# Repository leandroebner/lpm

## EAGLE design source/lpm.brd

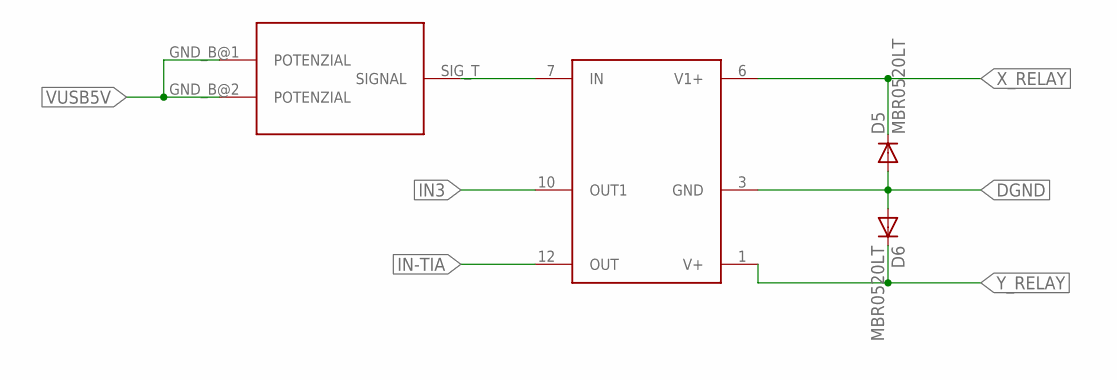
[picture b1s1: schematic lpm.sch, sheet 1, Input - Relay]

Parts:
D5, D6: MBR0520LT; SOD123
RELAY: DS1E; DIP12_8MM_X_13MM_DS1E
U$8: SMA_RAND; SMA-RAND-PRINT

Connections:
DGND: D5.A, D6.A, RELAY.3 (GND); also elsewhere on the board
IN3: RELAY.10 (OUT1); also elsewhere on the board
IN-TIA: RELAY.12 (OUT); also elsewhere on the board
IPD: RELAY.7 (IN), U$8.SIG_T (SIGNAL)
VUSB5V: U$8.GND_B@1 (POTENZIAL), U$8.GND_B@2 (POTENZIAL); also elsewhere on the board
X_RELAY: D5.C, RELAY.6 (V1+); also elsewhere on the board
Y_RELAY: D6.C, RELAY.1 (V+); also elsewhere on the board

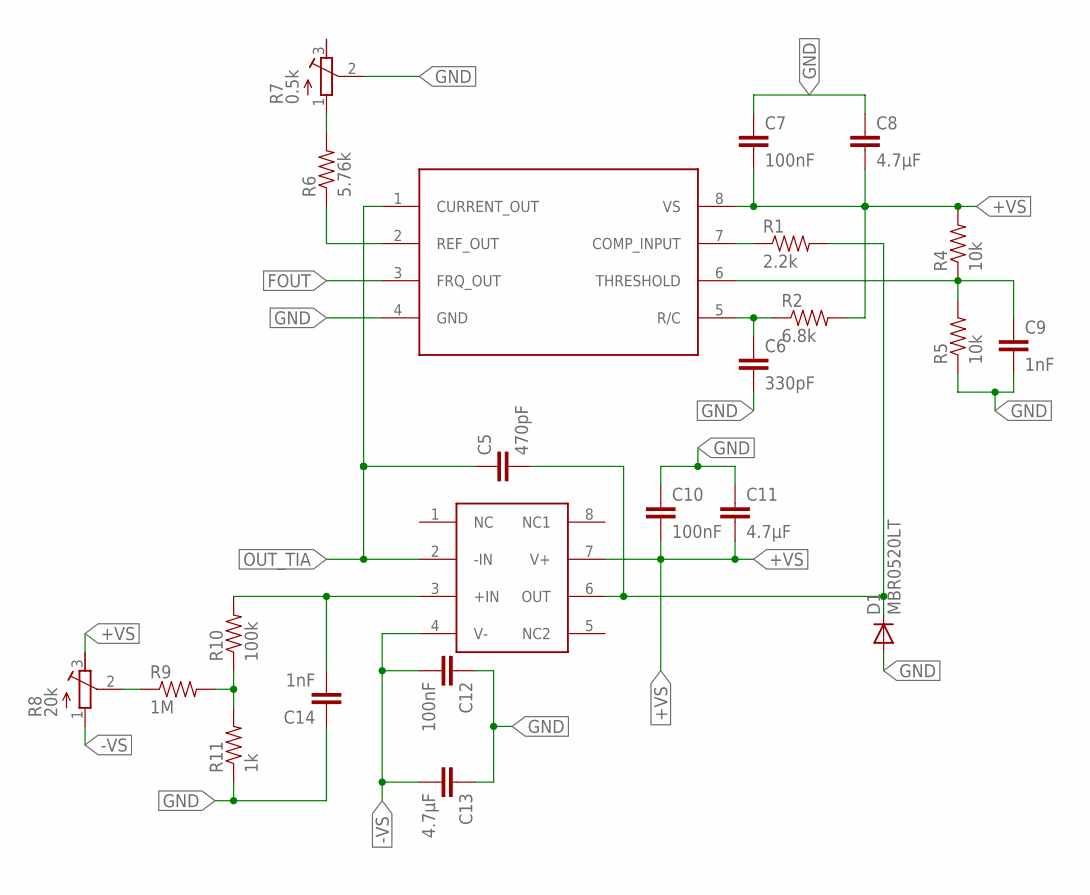
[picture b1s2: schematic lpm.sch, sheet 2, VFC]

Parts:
C5: 470pF; 0603-CAP
C6: 330pF; C0603K
C7, C10, C12: 100nF; C0603K
C8, C11, C13: 4.7µF; C0603K
C9, C14: 1nF; C0603K
D1: MBR0520LT; SOD123
R1: 2.2k; 0603-RES
R2: 6.8k; 0805
R4, R5: 10k; 0603-RES
R6: 5.76k; 0603-RES
R7: 0.5k; RTRIMTSM53YL
R8: 20k; RTRIMTS63Y
R9: 1M; 0603-RES
R10: 100k; 0603-RES
R11: 1k; 0603-RES
U$10: OPA191; SOIC8_4.90MMX3.91MM
VFC: LM331; DIP-08

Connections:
+VS: C7.2, C8.2, C10.2, C11.2, R2.2, R4.2, R8.3 (E), U$10.7 (V+), VFC.8 (VS); also elsewhere on the board
-VS: C12.2, C13.2, R8.1 (A), U$10.4 (V-); also elsewhere on the board
COMP_IN: R1.1, VFC.7 (COMP_INPUT)
FOUT: VFC.3 (FRQ_OUT); also elsewhere on the board
GND: C6.2, C7.1, C8.1, C9.2, C10.1, C11.1, C12.1, C13.1, C14.1, D1.A, R5.1, R7.2 (S), R11.1, VFC.4 (GND); also elsewhere on the board
IN+INTE: C14.2, R10.2, U$10.3 (+IN)
unnamed: C5.2, D1.C, R1.2, U$10.6 (OUT)
unnamed: C6.1, R2.1, VFC.5 (R/C)
unnamed: R6.1, VFC.2 (REF_OUT)
unnamed: C9.1, R4.1, R5.2, VFC.6 (THRESHOLD)
unnamed: R6.2, R7.1 (A)
unnamed: R9.2, R10.1, R11.2
unnamed: R8.2 (S), R9.1
OUT_TIA: C5.1, U$10.2 (-IN), VFC.1 (CURRENT_OUT); also elsewhere on the board

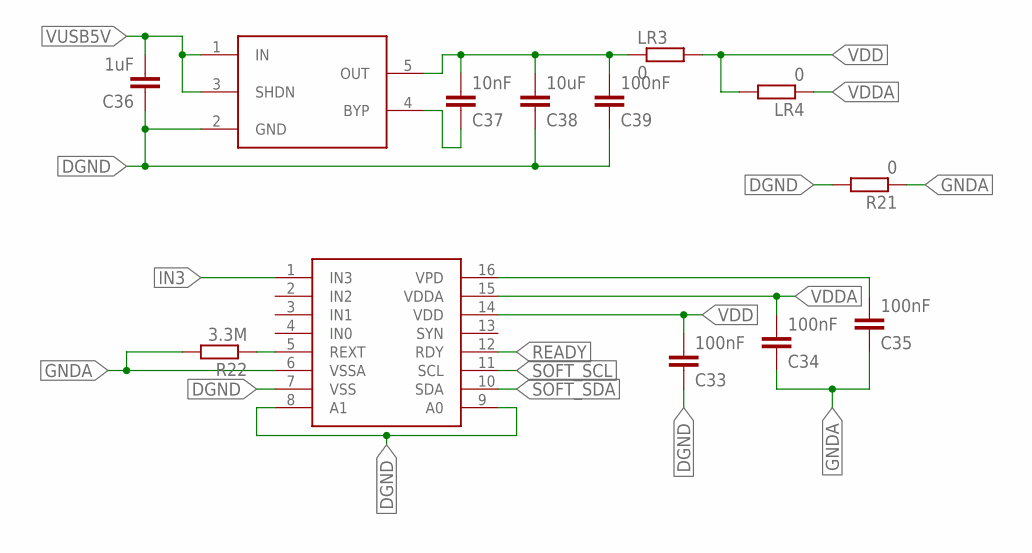
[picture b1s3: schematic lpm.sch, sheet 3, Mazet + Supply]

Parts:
C33, C34, C35, C39: 100nF; C0603
C36: 1uF; C0603
C37: 10nF; C0603
C38: 10uF; C0603
LDO1: LT1761; TSOT23-5
LR3, LR4: 0; R0603
MCDC01: MCDC04; SSOP16
R21: 0; R0603
R22: 3.3M; R0603

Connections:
DGND: C33.1, C36.1, C38.1, C39.1, LDO1.2 (GND), MCDC01.7 (VSS), MCDC01.8 (A1), MCDC01.9 (A0), R21.2; also elsewhere on the board
GNDA: C34.1, C35.1, MCDC01.6 (VSSA), R21.1, R22.2
IN3: MCDC01.1 (IN3); also elsewhere on the board
LDO_OUT3V1: C37.2, C38.2, C39.2, LDO1.5 (OUT), LR3.1
unnamed: C37.1, LDO1.4 (BYP)
READY: MCDC01.12 (RDY); also elsewhere on the board
REXT: MCDC01.5 (REXT), R22.1
SOFT_SCL: MCDC01.11 (SCL); also elsewhere on the board
SOFT_SDA: MCDC01.10 (SDA); also elsewhere on the board
VDD: C33.2, LR3.2, LR4.2, MCDC01.14 (VDD)
VDDA: C34.2, LR4.1, MCDC01.15 (VDDA)
VPD: C35.2, MCDC01.16 (VPD)
VUSB5V: C36.2, LDO1.1 (IN), LDO1.3 (SHDN); also elsewhere on the board

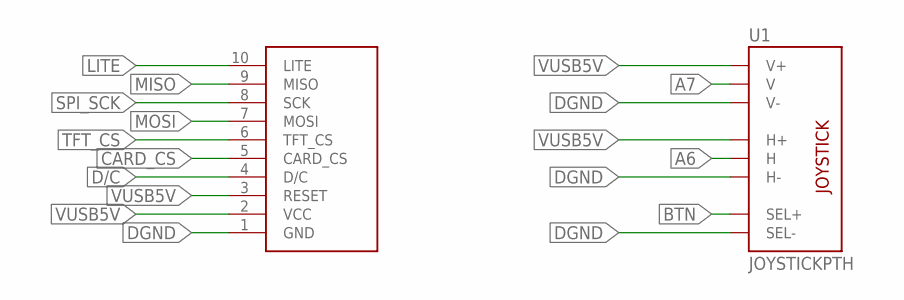
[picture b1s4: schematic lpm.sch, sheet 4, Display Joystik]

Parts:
DISPLAY: DISPLAY
U1: JOYSTICKPTH; JOYSTICK

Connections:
A6: U1.H2 (H); also elsewhere on the board
A7: U1.V2 (V); also elsewhere on the board
BTN: U1.B1A (SEL+); also elsewhere on the board
CARD_CS: DISPLAY.5 (CARD_CS); also elsewhere on the board
D/C: DISPLAY.4 (D/C); also elsewhere on the board
DGND: DISPLAY.1 (GND), U1.B2A (SEL-), U1.H3 (H-), U1.V3 (V-); also elsewhere on the board
LITE: DISPLAY.10 (LITE); also elsewhere on the board
MISO: DISPLAY.9 (MISO); also elsewhere on the board
MOSI: DISPLAY.7 (MOSI); also elsewhere on the board
SPI_SCK: DISPLAY.8 (SCK); also elsewhere on the board
TFT_CS: DISPLAY.6 (TFT_CS); also elsewhere on the board
VUSB5V: DISPLAY.2 (VCC), DISPLAY.3 (RESET), U1.H1 (H+), U1.V1 (V+); also elsewhere on the board

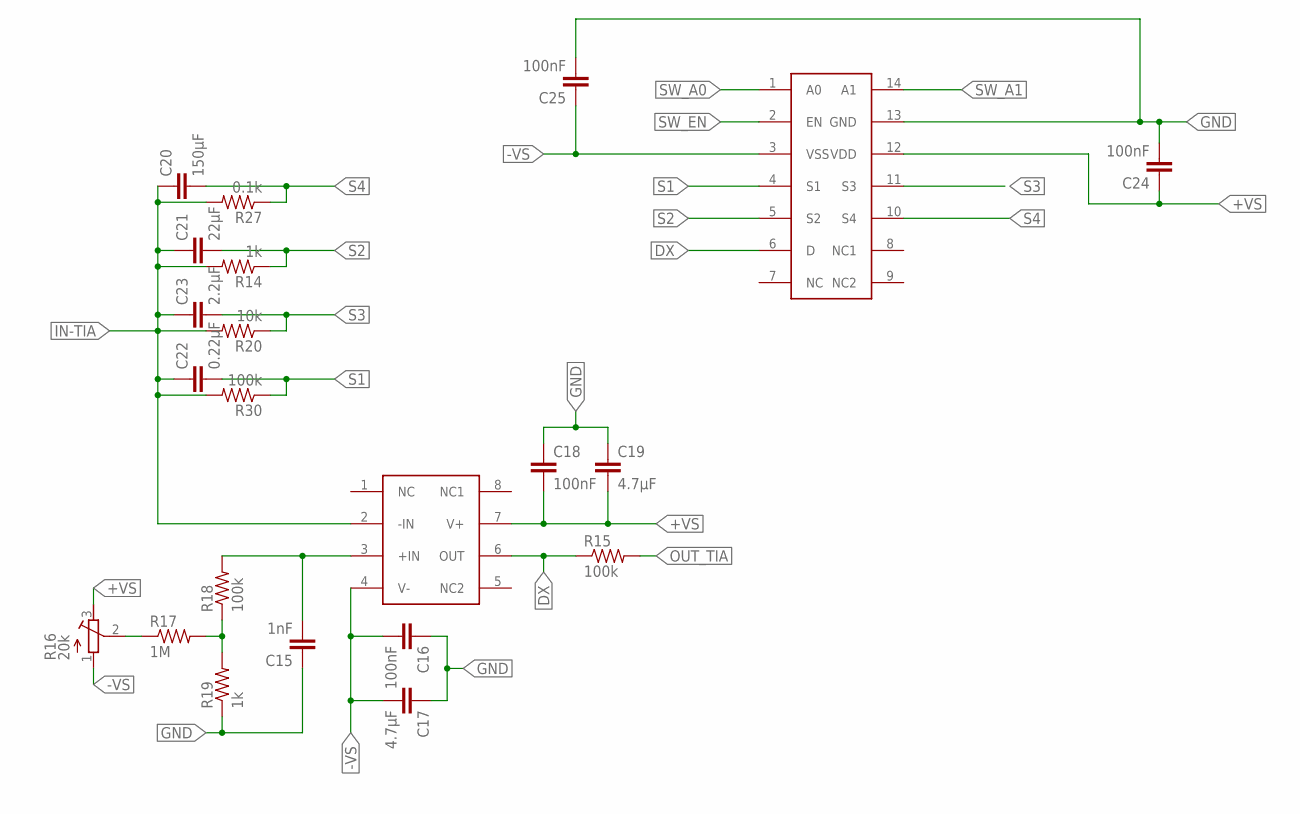
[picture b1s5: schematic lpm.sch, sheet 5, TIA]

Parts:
C15: 1nF; C0603K
C16, C18, C24, C25: 100nF; C0603K
C17, C19: 4.7µF; C0603K
C20: 150µF; C1206
C21: 22µF; C0805
C22: 0.22µF; C0603
C23: 2.2µF; C0805
R14, R19: 1k; 0603-RES
R15, R18, R30: 100k; 0603-RES
R16: 20k; RTRIMTS63Y
R17: 1M; 0603-RES
R20: 10k; 0603-RES
R27: 0.1k; 1206
U$1: ADG1404; TSSOP14-0.65-5X4.4MM
U$12: OPA191; SOIC8_4.90MMX3.91MM

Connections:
+VS: C18.2, C19.2, C24.1, R16.3 (E), U$1.12 (VDD), U$12.7 (V+); also elsewhere on the board
-VS: C16.2, C17.2, C25.1, R16.1 (A), U$1.3 (VSS), U$12.4 (V-); also elsewhere on the board
DX: R15.1, U$1.6 (D), U$12.6 (OUT)
GND: C15.1, C16.1, C17.1, C18.1, C19.1, C24.2, C25.2, R19.1, U$1.13 (GND); also elsewhere on the board
IN+TIA: C15.2, R18.2, U$12.3 (+IN)
IN-TIA: C20.1, C21.1, C22.1, C23.1, R14.2, R20.2, R27.2, R30.2, U$12.2 (-IN); also elsewhere on the board
unnamed: R17.2, R18.1, R19.2
unnamed: R16.2 (S), R17.1
OUT_TIA: R15.2; also elsewhere on the board
S1: C22.2, R30.1, U$1.4 (S1)
S2: C21.2, R14.1, U$1.5 (S2)
S3: C23.2, R20.1, U$1.11 (S3)
S4: C20.2, R27.1, U$1.10 (S4)
SW_A0: U$1.1 (A0); also elsewhere on the board
SW_A1: U$1.14 (A1); also elsewhere on the board
SW_EN: U$1.2 (EN); also elsewhere on the board

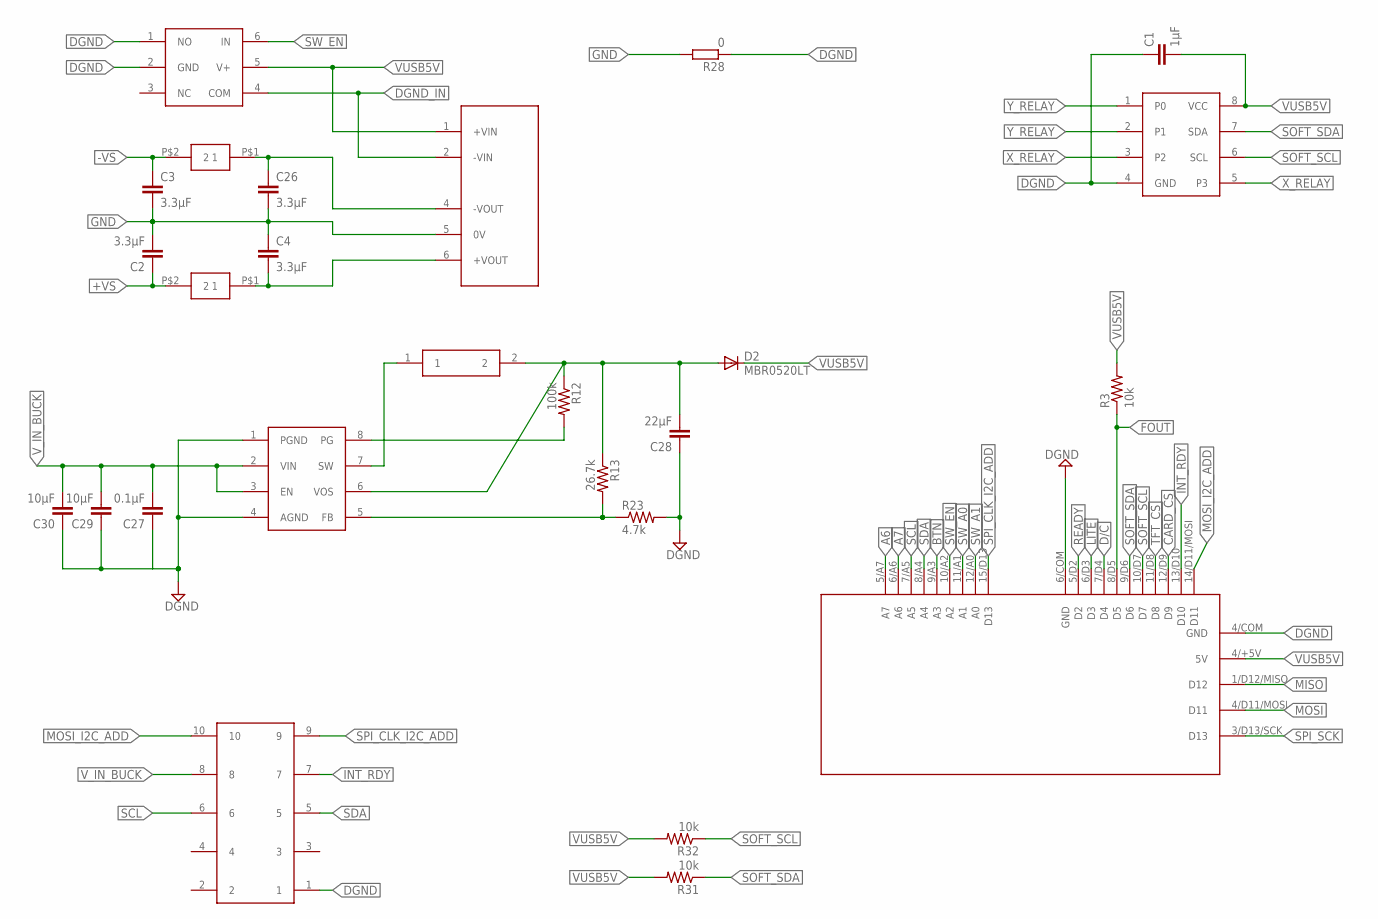
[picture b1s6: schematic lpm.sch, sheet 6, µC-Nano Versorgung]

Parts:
C1: 1µF; C0603K
C2, C3, C4, C26: 3.3µF; C0603K
C27: 0.1µF; C0603K
C28: 22µF; C0603K
C29, C30: 10µF; C0603K
D2: MBR0520LT; SOD123
R3, R31, R32: 10k; 0603-RES
R12: 100k; 0603-RES
R13: 26.7k; 0603-RES
R23: 4.7k; 0603-RES
R28: 0; R0603
U$2, U$4: KMP_100µH; KMP
U$3: HEADER_10POL; BOX_HEADER_2.54MM
U$6: TS5A3159A; SOT23-6
U$7: 0; SOIC8_4.90MMX3.91MM
U$9: LPS3015
U$11: NMA0515SC; SIP7
U$13: NANO_V2
U$14: TPS62160; POWER-SOP8

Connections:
5.5VBUCK: C28.2, D2.A, R12.1, R13.1, U$9.2, U$14.6 (VOS)
+VS: C2.1, U$4.P$2 (2); also elsewhere on the board
-VS: C3.1, U$2.P$2 (2); also elsewhere on the board
A6: U$13.5/A7 (A7); also elsewhere on the board
A7: U$13.6/A6 (A6); also elsewhere on the board
BTN: U$13.9/A3 (A3); also elsewhere on the board
CARD_CS: U$13.12/D9 (D9); also elsewhere on the board
D/C: U$13.7/D4 (D4); also elsewhere on the board
DGND: C1.1, C27.1, C28.1, C29.1, C30.1, R23.2, R28.1, U$3.1, U$6.1 (NO), U$6.2 (GND), U$7.4 (GND), U$13.4/COM (GND), U$13.6/COM (GND), U$14.1 (PGND), U$14.4 (AGND); also elsewhere on the board
DGND_IN: U$6.4 (COM), U$11.2 (-VIN)
FOUT: R3.1, U$13.8/D5 (D5); also elsewhere on the board
GND: C2.2, C3.2, C4.1, C26.2, R28.2, U$11.5 (0V); also elsewhere on the board
INT_RDY: U$3.7, U$13.13/D10 (D10)
LITE: U$13.6/D3 (D3); also elsewhere on the board
MISO: U$13.1/D12/MISO (D12); also elsewhere on the board
MOSI: U$13.4/D11/MOSI (D11); also elsewhere on the board
MOSI_I2C_ADD: U$3.10, U$13.14/D11/MOSI (D11)
unnamed: C4.2, U$4.P$1 (1), U$11.6 (+VOUT)
unnamed: C26.1, U$2.P$1 (1), U$11.4 (-VOUT)
unnamed: R13.2, R23.1, U$14.5 (FB)
unnamed: R12.2, U$14.8 (PG)
unnamed: U$9.1, U$14.7 (SW)
READY: U$13.5/D2 (D2); also elsewhere on the board
SCL: U$3.6, U$13.7/A5 (A5)
SDA: U$3.5, U$13.8/A4 (A4)
SOFT_SCL: R32.1, U$7.6 (SCL), U$13.10/D7 (D7); also elsewhere on the board
SOFT_SDA: R31.1, U$7.7 (SDA), U$13.9/D6 (D6); also elsewhere on the board
SPI_CLK_I2C_ADD: U$3.9, U$13.15/D13 (D13)
SPI_SCK: U$13.3/D13/SCK (D13); also elsewhere on the board
SW_A0: U$13.11/A1 (A1); also elsewhere on the board
SW_A1: U$13.12/A0 (A0); also elsewhere on the board
SW_EN: U$6.6 (IN), U$13.10/A2 (A2); also elsewhere on the board
TFT_CS: U$13.11/D8 (D8); also elsewhere on the board
VUSB5V: C1.2, D2.C, R3.2, R31.2, R32.2, U$6.5 (V+), U$7.8 (VCC), U$11.1 (+VIN), U$13.4/+5V (5V); also elsewhere on the board
V_IN_BUCK: C27.2, C29.2, C30.2, U$3.8, U$14.2 (VIN), U$14.3 (EN)
X_RELAY: U$7.3 (P2), U$7.5 (P3); also elsewhere on the board
Y_RELAY: U$7.1 (P0), U$7.2 (P1); also elsewhere on the board

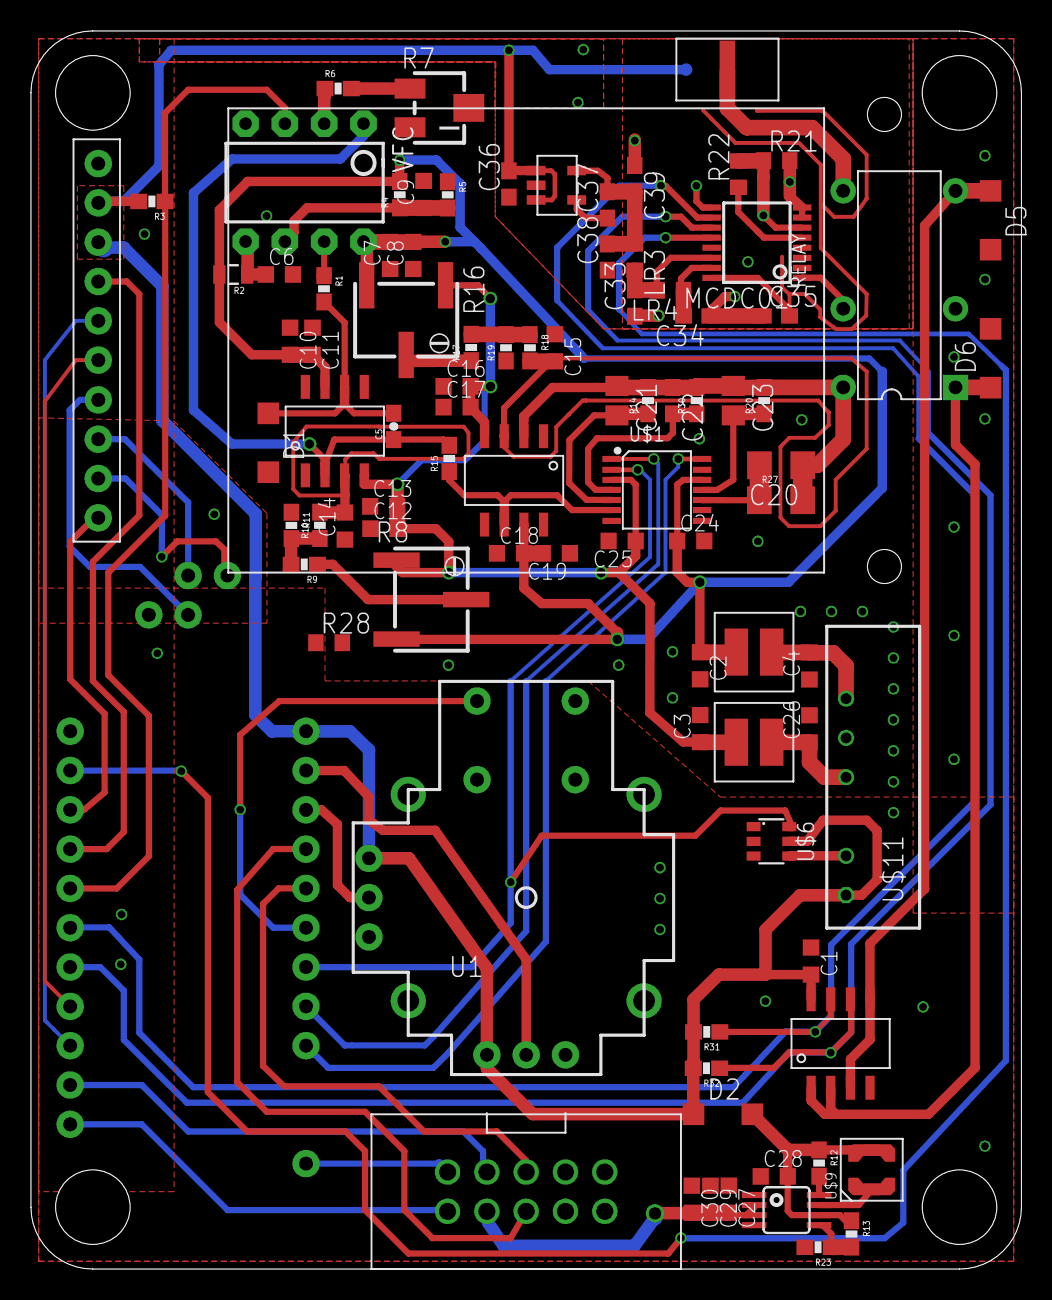
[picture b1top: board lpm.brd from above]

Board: 2 copper layers, 64.0 x 80.0 mm, 90 parts (0 on the bottom side), 65 nets.

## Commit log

2024-01-01 added source files

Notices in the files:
parts and their libraries:
SparkFun-Passives: Licensing: Creative Commons ShareAlike 4.0 International - https://creativecommons.org/licenses/by-sa/4.0
